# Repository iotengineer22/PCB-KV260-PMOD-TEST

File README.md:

# PCB-KV260-PMOD-TEST
PCB-KV260(KR260)-PMOD-INOUT(LED/SW)-PCB-KiCad-DATA

# DEMO

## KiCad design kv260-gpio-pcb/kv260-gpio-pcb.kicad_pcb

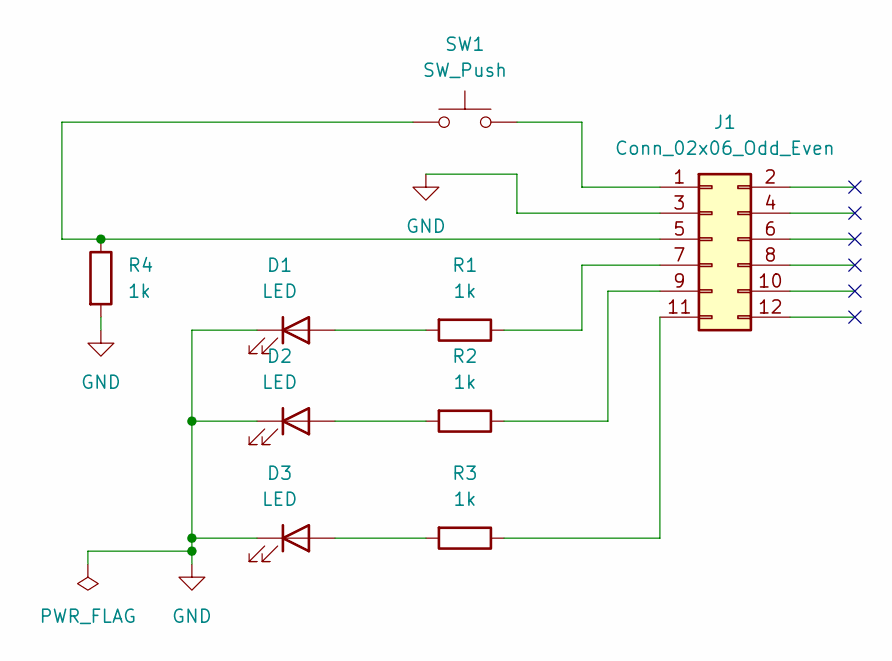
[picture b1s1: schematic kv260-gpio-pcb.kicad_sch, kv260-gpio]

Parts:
D1, D2, D3: LED; LED_D3.0mm
J1: Conn_02x06_Odd_Even; PinHeader_2x06_P2.54mm_Horizontal
R1, R2, R3, R4: 1k; R_Axial_DIN0207_L6.3mm_D2.5mm_P10.16mm_Horizontal
SW1: SW_Push; SW_PUSH_6mm_H4.3mm

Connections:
GND: D1.1 (K), D2.1 (K), D3.1 (K), J1.3, R4.2
unnamed: D1.2 (A), R1.2
unnamed: D2.2 (A), R2.2
unnamed: D3.2 (A), R3.2
unnamed: J1.1, SW1.1
unnamed: J1.5, R4.1, SW1.2
unnamed: J1.7, R1.1
unnamed: J1.9, R2.1
unnamed: J1.11, R3.1

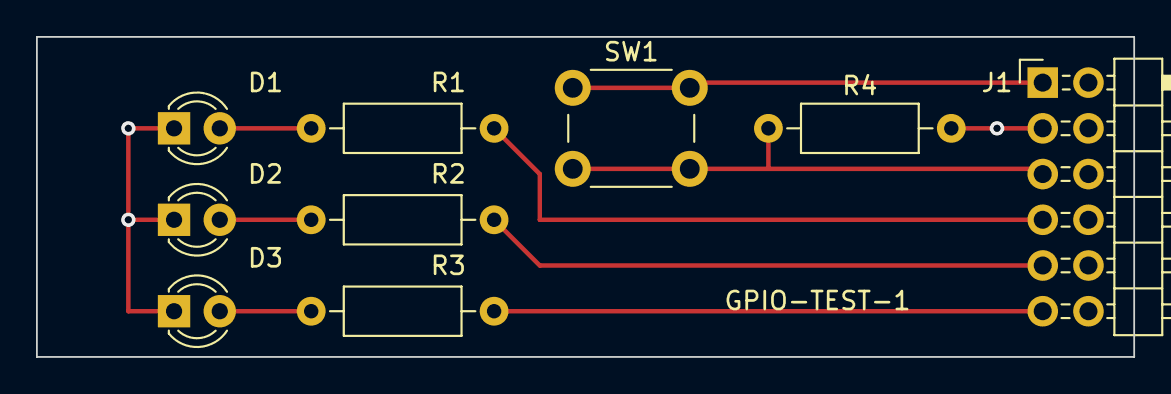
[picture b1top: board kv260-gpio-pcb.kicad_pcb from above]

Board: 2 copper layers, 61.0 x 17.8 mm, 9 parts (0 on the bottom side), 9 nets.

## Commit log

2024-02-11 Add files via upload
    files_input
2024-02-11 Update README.md
    readme-update
